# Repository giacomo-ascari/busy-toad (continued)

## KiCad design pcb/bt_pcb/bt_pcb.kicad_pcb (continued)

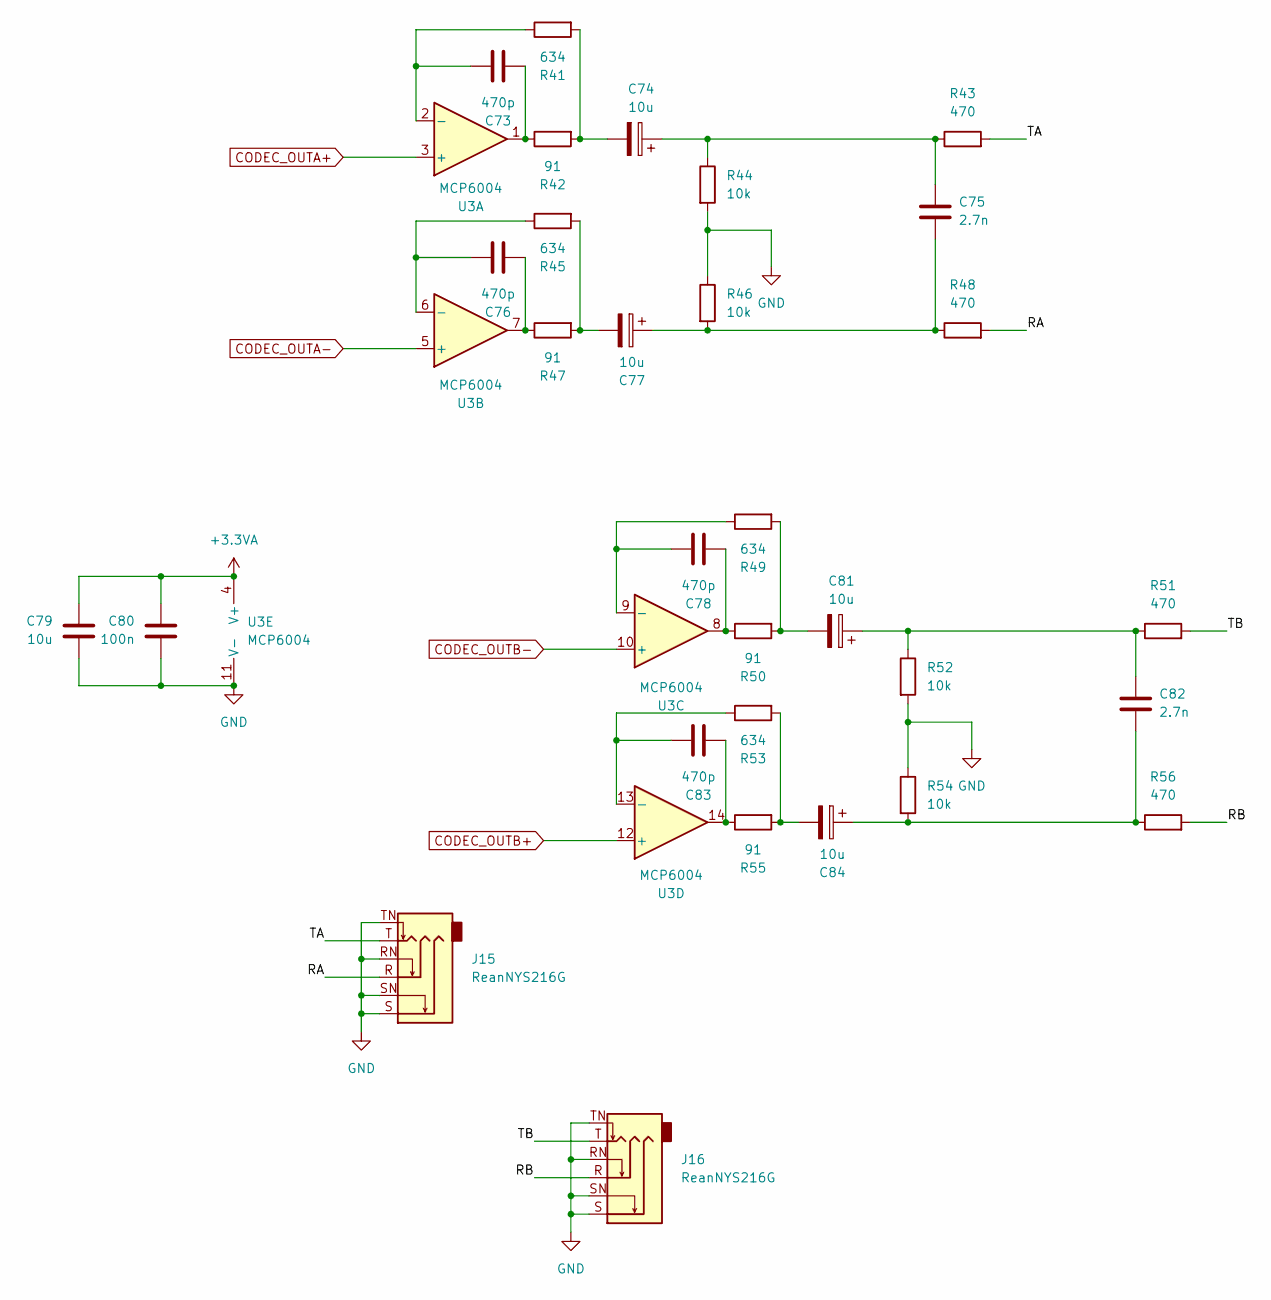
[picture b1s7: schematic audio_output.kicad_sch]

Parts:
C73, C76, C78, C83: 470p; C_0603_1608Metric_Pad1.08x0.95mm_HandSolder
C74, C77, C79, C81, C84: 10u; C_0805_2012Metric_Pad1.18x1.45mm_HandSolder
C75, C82: 2.7n; C_0603_1608Metric_Pad1.08x0.95mm_HandSolder
C80: 100n; C_0603_1608Metric_Pad1.08x0.95mm_HandSolder
J15, J16: ReanNYS216G; NYS-216G
R41, R45, R49, R53: 634; R_0603_1608Metric_Pad0.98x0.95mm_HandSolder
R42, R47, R50, R55: 91; R_0603_1608Metric_Pad0.98x0.95mm_HandSolder
R43, R48, R51, R56: 470; R_0603_1608Metric_Pad0.98x0.95mm_HandSolder
R44, R46, R52, R54: 10k; R_0603_1608Metric_Pad0.98x0.95mm_HandSolder
U3: MCP6004; TSSOP-14_4.4x5mm_P0.65mm

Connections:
+3.3VA: C79.1, C80.1, U3.4 (V+); also elsewhere on the board
/Codec and audio IO/Audio ouput/RA: J15.R, R48.2
/Codec and audio IO/Audio ouput/RB: J16.R, R56.2
/Codec and audio IO/Audio ouput/TA: J15.T, R43.2
/Codec and audio IO/Audio ouput/TB: J16.T, R51.2
CODEC_OUTA+: U3.3 (+); also elsewhere on the board
CODEC_OUTA-: U3.5 (+); also elsewhere on the board
CODEC_OUTB+: U3.12 (+); also elsewhere on the board
CODEC_OUTB-: U3.10 (+); also elsewhere on the board
GND: C79.2, C80.2, J15.RN, J15.S, J15.SN, J15.TN, J16.RN, J16.S, J16.SN, J16.TN, R44.2, R46.1, R52.2, R54.1, U3.11 (V-); also elsewhere on the board
unnamed: C73.1, R42.1, U3.1
unnamed: C74.1, C75.1, R43.1, R44.1
unnamed: C74.2, R41.2, R42.2
unnamed: C75.2, C77.1, R46.2, R48.1
unnamed: C76.1, R47.1, U3.7
unnamed: C77.2, R45.2, R47.2
unnamed: C78.1, R50.1, U3.8
unnamed: C81.1, C82.1, R51.1, R52.1
unnamed: C81.2, R49.2, R50.2
unnamed: C82.2, C84.1, R54.2, R56.1
unnamed: C83.1, R55.1, U3.14
unnamed: C84.2, R53.2, R55.2
unnamed: C73.2, R41.1, U3.2 (-)
unnamed: C76.2, R45.1, U3.6 (-)
unnamed: C78.2, R49.1, U3.9 (-)
unnamed: C83.2, R53.1, U3.13 (-)

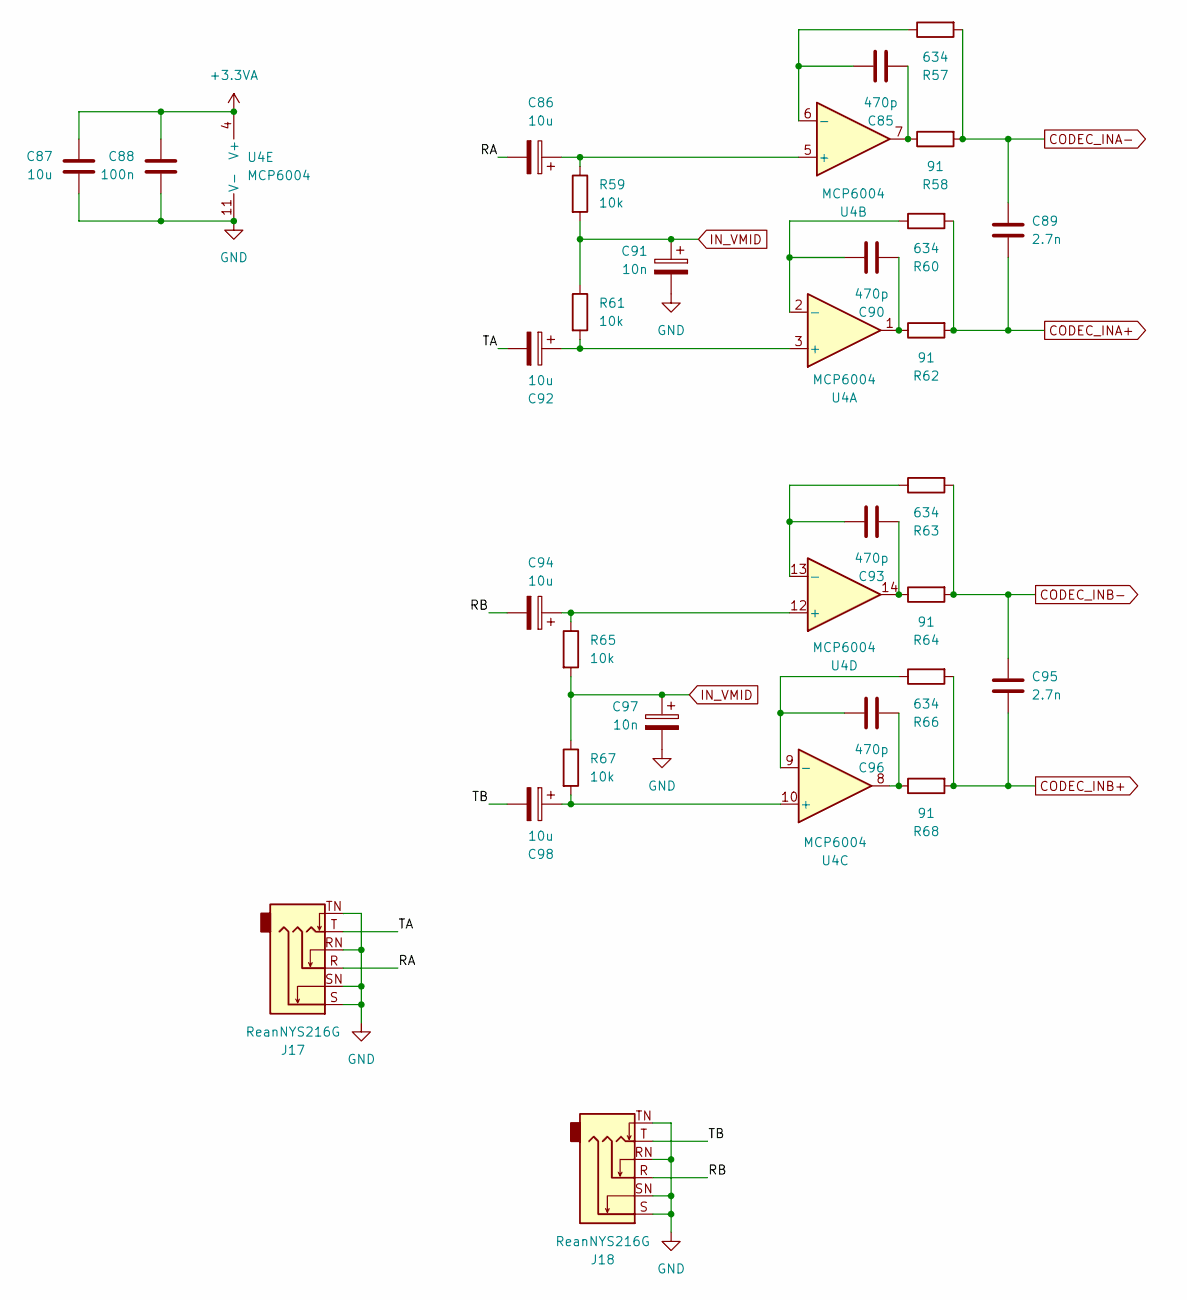
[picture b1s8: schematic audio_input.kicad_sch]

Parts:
C85, C90, C93, C96: 470p; C_0603_1608Metric_Pad1.08x0.95mm_HandSolder
C86, C87, C92, C94, C98: 10u; C_0805_2012Metric_Pad1.18x1.45mm_HandSolder
C88: 100n; C_0603_1608Metric_Pad1.08x0.95mm_HandSolder
C89, C95: 2.7n; C_0603_1608Metric_Pad1.08x0.95mm_HandSolder
C91, C97: 10n; C_0603_1608Metric_Pad1.08x0.95mm_HandSolder
J17, J18: ReanNYS216G; NYS-216G
R57, R60, R63, R66: 634; R_0603_1608Metric_Pad0.98x0.95mm_HandSolder
R58, R62, R64, R68: 91; R_0603_1608Metric_Pad0.98x0.95mm_HandSolder
R59, R61, R65, R67: 10k; R_0603_1608Metric_Pad0.98x0.95mm_HandSolder
U4: MCP6004; TSSOP-14_4.4x5mm_P0.65mm

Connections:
+3.3VA: C87.1, C88.1, U4.4 (V+); also elsewhere on the board
/Codec and audio IO/Audio input/RA: C86.2, J17.R
/Codec and audio IO/Audio input/RB: C94.2, J18.R
/Codec and audio IO/Audio input/TA: C92.2, J17.T
/Codec and audio IO/Audio input/TB: C98.2, J18.T
CODEC_INA+: C89.2, R60.2, R62.2; also elsewhere on the board
CODEC_INA-: C89.1, R57.2, R58.2; also elsewhere on the board
CODEC_INB+: C95.2, R66.2, R68.2; also elsewhere on the board
CODEC_INB-: C95.1, R63.2, R64.2; also elsewhere on the board
GND: C87.2, C88.2, C91.2, C97.2, J17.RN, J17.S, J17.SN, J17.TN, J18.RN, J18.S, J18.SN, J18.TN, U4.11 (V-); also elsewhere on the board
IN_VMID: C91.1, C97.1, R59.2, R61.1, R65.2, R67.1; also elsewhere on the board
unnamed: C85.1, R58.1, U4.7
unnamed: C90.1, R62.1, U4.1
unnamed: C93.1, R64.1, U4.14
unnamed: C96.1, R68.1, U4.8
unnamed: C92.1, R61.2, U4.3 (+)
unnamed: C90.2, R60.1, U4.2 (-)
unnamed: C86.1, R59.1, U4.5 (+)
unnamed: C85.2, R57.1, U4.6 (-)
unnamed: C98.1, R67.2, U4.10 (+)
unnamed: C96.2, R66.1, U4.9 (-)
unnamed: C94.1, R65.1, U4.12 (+)
unnamed: C93.2, R63.1, U4.13 (-)

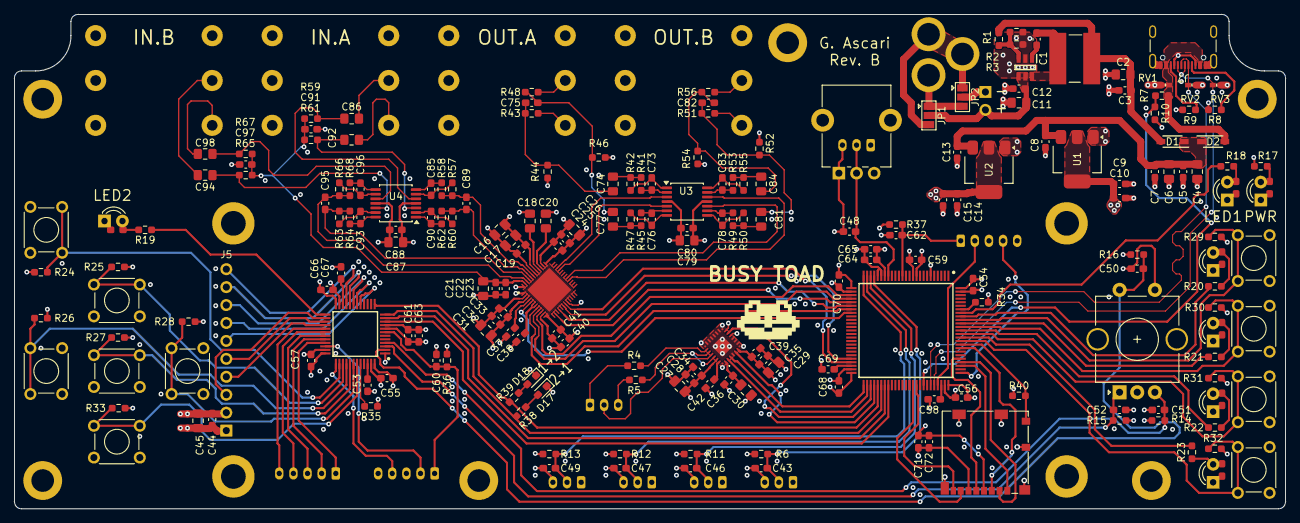
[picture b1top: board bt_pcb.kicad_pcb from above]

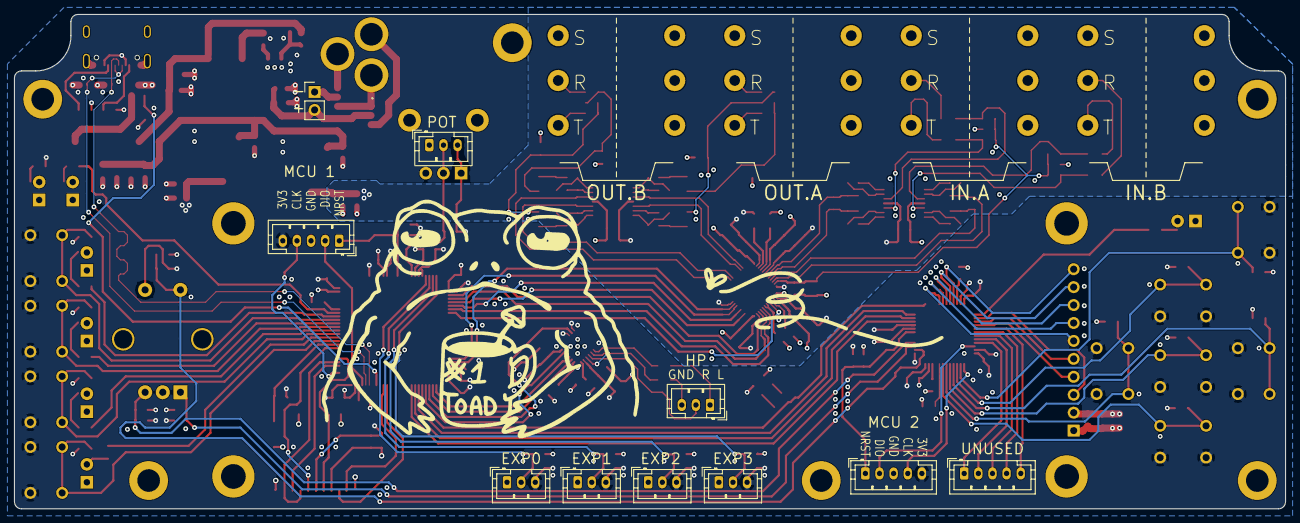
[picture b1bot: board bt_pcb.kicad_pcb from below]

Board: 4 copper layers, 180.0 x 70.0 mm, 235 parts (15 on the bottom side), 154 nets.

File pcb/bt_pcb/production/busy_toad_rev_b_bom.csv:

Designator,Footprint,Quantity,Value,LCSC Part #
"C1, C10, C12, C15, C19, C22, C23, C24, C3, C33, C34, C36, C39, C41, C43, C44, C46, C47, C48, C49, C5, C50, C51, C52, C54, C55, C56, C57, C59, C60, C61, C62, C64, C66, C68, C7, C70, C80, C88",0603,39,100n,
"C11, C17, C2, C26, C27, C29, C30, C31, C4, C45, C6, C74, C77, C79, C81, C84, C86, C87, C92, C94, C98",0805,21,10u,
"C13, C25, C28, C32, C35, C37, C38, C40, C42, C63, C65, C8",0603,12,1u,
"C14, C53, C58, C67, C69, C71, C72, C9",0603,8,2.2u,
"C16, C18, C20, C21",0805,4,22u,
"C73, C76, C78, C83, C85, C90, C93, C96",0603,8,470p,
"C75, C82, C89, C95",0603,4,2.7n,
"C91, C97",0603,2,10n,
"D1, D2",SOD3716X125N,2,B5819W,
"D10, D12, D14, D16, D4, D6, D8",LED_D3.0mm,7,LED,
"D11, D13, D15, D17, D18, D3, D5, D7, D9",0603,9,LED,
IC1,SOT95P280X145-6N,1,LV3842XDBVR,
IC2,QFN40P600X600X80-49N-D,1,CS4282P,
IC3,TAD5242IRGER,1,TAD5242IRGER,
IC4,QFP50P1600X1600X160-100N,1,STM32H750VBT6,
IC5,QFP50P900X900X160-48N,1,STM32H523CET6,
J14,microSD_HC_Molex_104031-0811,1,Micro_SD_Card_Det2,
"J15, J16, J17, J18",NYS-216G,4,ReanNYS216G,
J2,694106301002_1,1,Barrel_Jack_Switch,
J7,USB_C_Receptacle_GCT_USB4105-xx-A_16P_TopMnt_Horizontal,1,USB_C_Receptacle_USB2.0_16P,
L1,SRR6040A180M,1,18uH 1.5A,
R1,0603,1,100k,
"R10, R11, R12, R13, R14, R15, R16, R24, R25, R26, R27, R28, R29, R30, R31, R32, R33, R34, R35, R36, R37, R40, R44, R46, R52, R54, R59, R6, R61, R65, R67",0603,31,10k,
"R17, R18, R19, R20, R21, R22, R23",0603,7,680/510,
"R2, R3",0603,2,47k,
"R38, R39",0603,2,680,
"R4, R5",0603,2,22,
"R41, R45, R49, R53, R57, R60, R63, R66",0603,8,634,
"R42, R47, R50, R55, R58, R62, R64, R68",0603,8,91,
"R43, R48, R51, R56",0603,4,470,
R7,0603,1,4k7,
"R8, R9",0603,2,5k1,
"RV1, RV2, RV3",VARC1005X41N,3,CG0402MLU-12G,
RV4,Potentiometer_Alpha_RD901F-40-00D_Single_Vertical_CircularHoles,1,R_Potentiometer,
SW1,RotaryEncoder_Alps_EC11E-Switch_Vertical_H20mm_CircularMountingHoles,1,RotaryEncoder_Switch,
"SW10, SW11, SW2, SW3, SW4, SW5, SW6, SW7, SW8, SW9",SW_TH_Tactile_Omron_B3F-102x,10,SW_Push,
"U1, U2",SOT-223-3_TabPin2,2,TLV76133DCY,
"U3, U4",TSSOP-14_4.4x5mm_P0.65mm,2,MCP6004,

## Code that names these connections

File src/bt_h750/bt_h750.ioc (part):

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Mcu.Name=STM32H750VBTx
Mcu.Package=LQFP100
Mcu.UserName=STM32H750VBTx
PA0.GPIOParameters=GPIO_Label
PA0.GPIO_Label=EXP_0
PA0.Mode=IN16-Single-Ended
PA0.Signal=ADC1_INP16
PA1.GPIOParameters=GPIO_Label
PA1.GPIO_Label=EXP_1
PA1.Mode=IN17-Single-Ended
PA1.Signal=ADC1_INP17
PA10.GPIOParameters=GPIO_Label,GPIO_Pd
PA10.GPIO_Label=X
PA10.GPIO_Pd=GPIO_PULLDOWN
PA10.Signal=GPIO_Analog
PA11.Mode=Device_Only
PA11.Signal=USB_OTG_FS_DM
PA12.Mode=Device_Only
PA12.Signal=USB_OTG_FS_DP
PA13\ (JTMS/SWDIO).Mode=Serial_Wire
PA13\ (JTMS/SWDIO).Signal=DEBUG_JTMS-SWDIO
PA14\ (JTCK/SWCLK).Mode=Serial_Wire
PA14\ (JTCK/SWCLK).Signal=DEBUG_JTCK-SWCLK
PA15\ (JTDI).GPIOParameters=GPIO_Label,GPIO_Pd
PA15\ (JTDI).GPIO_Label=X
PA15\ (JTDI).GPIO_Pd=GPIO_PULLDOWN
PA15\ (JTDI).Signal=GPIO_Analog
PA2.GPIOParameters=GPIO_Label
PA2.GPIO_Label=EXP_2
PA2.Signal=ADCx_INP14
PA3.GPIOParameters=GPIO_Label
PA3.GPIO_Label=EXP_3
PA3.Signal=ADCx_INP15
PA4.GPIOParameters=GPIO_Label
PA4.GPIO_Label=CODEC_I2S_WS
PA4.Mode=Full_Duplex_Master
PA4.Signal=I2S1_WS
PA5.GPIOParameters=GPIO_Label
PA5.GPIO_Label=CODEC_I2S_CK
PA5.Mode=Full_Duplex_Master
PA5.Signal=I2S1_CK
PA6.GPIOParameters=GPIO_Label
PA6.GPIO_Label=CODEC_I2S_SDI
PA6.Mode=Full_Duplex_Master
PA6.Signal=I2S1_SDI
PA7.GPIOParameters=GPIO_Label
PA7.GPIO_Label=CODEC_I2S_SDO
PA7.Mode=Full_Duplex_Master
PA7.Signal=I2S1_SDO
PA8.GPIOParameters=GPIO_Label,GPIO_Pd
PA8.GPIO_Label=X
PA8.GPIO_Pd=GPIO_PULLDOWN
PA8.Signal=GPIO_Analog
PA9.Mode=Activate_VBUS
PA9.Signal=USB_OTG_FS_VBUS
PB0.GPIOParameters=GPIO_Label,GPIO_Pd
PB0.GPIO_Label=X
PB0.GPIO_Pd=GPIO_PULLDOWN
PB0.Signal=GPIO_Analog
PB1.GPIOParameters=GPIO_Label,GPIO_Pd
PB1.GPIO_Label=X
PB1.GPIO_Pd=GPIO_PULLDOWN
PB1.Signal=GPIO_Analog
PB10.GPIOParameters=GPIO_Speed,GPIO_Label,GPIO_Pu
PB10.GPIO_Label=CODEC_I2C_SCL
PB10.GPIO_Pu=GPIO_NOPULL
PB10.GPIO_Speed=GPIO_SPEED_FREQ_LOW
PB10.Mode=I2C
PB10.Signal=I2C2_SCL
PB11.GPIOParameters=GPIO_Speed,GPIO_Label,GPIO_Pu
PB11.GPIO_Label=CODEC_I2C_SDA
PB11.GPIO_Pu=GPIO_NOPULL
PB11.GPIO_Speed=GPIO_SPEED_FREQ_LOW
PB11.Mode=I2C
PB11.Signal=I2C2_SDA
PB12.GPIOParameters=GPIO_Speed,GPIO_Label
PB12.GPIO_Label=HPDAC_I2S_WS
PB12.GPIO_Speed=GPIO_SPEED_FREQ_LOW
PB12.Mode=Full_Duplex_Master
PB12.Signal=I2S2_WS
PB13.GPIOParameters=GPIO_Speed,GPIO_Label
PB13.GPIO_Label=HPDAC_I2S_BCK
PB13.GPIO_Speed=GPIO_SPEED_FREQ_LOW
PB13.Mode=Full_Duplex_Master
PB13.Signal=I2S2_CK
PB14.GPIOParameters=GPIO_Speed,GPIO_Label
PB14.GPIO_Label=HPDAC_I2S_SDI
PB14.GPIO_Speed=GPIO_SPEED_FREQ_LOW
PB14.Mode=Full_Duplex_Master
PB14.Signal=I2S2_SDI
PB15.GPIOParameters=GPIO_Speed,GPIO_Label
PB15.GPIO_Label=HPDAC_I2S_SDO
PB15.GPIO_Speed=GPIO_SPEED_FREQ_LOW
PB15.Mode=Full_Duplex_Master
PB15.Signal=I2S2_SDO
PB2.GPIOParameters=GPIO_Label,GPIO_Pd
PB2.GPIO_Label=X
PB2.GPIO_Pd=GPIO_PULLDOWN
PB2.Signal=GPIO_Analog
PB3\ (JTDO/TRACESWO).GPIOParameters=GPIO_Label
PB3\ (JTDO/TRACESWO).GPIO_Label=BTN_B
PB3\ (JTDO/TRACESWO).Signal=GPIO_Input
PB4\ (NJTRST).GPIOParameters=GPIO_Label
PB4\ (NJTRST).GPIO_Label=LED_B
PB4\ (NJTRST).Signal=GPIO_Output
PB5.GPIOParameters=GPIO_Label
PB5.GPIO_Label=BTN_A
PB5.Signal=GPIO_Input
PB6.GPIOParameters=GPIO_Label
PB6.GPIO_Label=LED_A
PB6.Signal=GPIO_Output
PB7.GPIOParameters=GPIO_Label
PB7.GPIO_Label=LED_RD
PB7.Signal=GPIO_Output
PB8.GPIOParameters=GPIO_Label,GPIO_Pd
PB8.GPIO_Label=X
PB8.GPIO_Pd=GPIO_PULLDOWN
PB8.Signal=GPIO_Analog
PB9.GPIOParameters=GPIO_Label,GPIO_Pd
PB9.GPIO_Label=X
PB9.GPIO_Pd=GPIO_PULLDOWN
PB9.Signal=GPIO_Analog
PC0.GPIOParameters=GPIO_Label,GPIO_Pd
PC0.GPIO_Label=X
PC0.GPIO_Pd=GPIO_PULLDOWN
PC0.Signal=GPIO_Analog
PC1.GPIOParameters=GPIO_Label,GPIO_Pd
PC1.GPIO_Label=X
PC1.GPIO_Pd=GPIO_PULLDOWN
PC1.Signal=GPIO_Analog
PC10.GPIOParameters=GPIO_PuPd,GPIO_Speed_High_Default,GPIO_Label
PC10.GPIO_Label=SD_D2
PC10.GPIO_PuPd=GPIO_PULLUP
PC10.GPIO_Speed_High_Default=GPIO_SPEED_FREQ_LOW
PC10.Mode=SD_4_bits_Wide_bus
PC10.Signal=SDMMC1_D2
PC11.GPIOParameters=GPIO_PuPd,GPIO_Speed_High_Default,GPIO_Label
PC11.GPIO_Label=SD_D3
PC11.GPIO_PuPd=GPIO_PULLUP
PC11.GPIO_Speed_High_Default=GPIO_SPEED_FREQ_LOW
PC11.Mode=SD_4_bits_Wide_bus
PC11.Signal=SDMMC1_D3
PC12.GPIOParameters=GPIO_Speed_High_Default,GPIO_Label
PC12.GPIO_Label=SD_CK
PC12.GPIO_Speed_High_Default=GPIO_SPEED_FREQ_LOW
PC12.Mode=SD_4_bits_Wide_bus
PC12.Signal=SDMMC1_CK
PC13.GPIOParameters=GPIO_Label,GPIO_Pd
PC13.GPIO_Label=X
PC13.GPIO_Pd=GPIO_PULLDOWN
PC13.Signal=GPIO_Analog
PC14-OSC32_IN\ (OSC32_IN).GPIOParameters=GPIO_Label,GPIO_Pd
PC14-OSC32_IN\ (OSC32_IN).GPIO_Label=X
PC14-OSC32_IN\ (OSC32_IN).GPIO_Pd=GPIO_PULLDOWN
PC14-OSC32_IN\ (OSC32_IN).Signal=GPIO_Analog
PC15-OSC32_OUT\ (OSC32_OUT).GPIOParameters=GPIO_Label,GPIO_Pd
PC15-OSC32_OUT\ (OSC32_OUT).GPIO_Label=X
PC15-OSC32_OUT\ (OSC32_OUT).GPIO_Pd=GPIO_PULLDOWN
PC15-OSC32_OUT\ (OSC32_OUT).Signal=GPIO_Analog
PC2_C.GPIOParameters=GPIO_Label,GPIO_Pd
PC2_C.GPIO_Label=X
PC2_C.GPIO_Pd=GPIO_PULLDOWN
PC2_C.Signal=GPIO_Analog
PC3_C.GPIOParameters=GPIO_Label
PC3_C.GPIO_Label=POT_0
PC3_C.Mode=IN1-Single-Ended
PC3_C.Signal=ADC3_INP1
PC4.GPIOParameters=GPIO_Label
PC4.GPIO_Label=CODEC_I2S_MCK
PC4.Mode=Master_Clock_Activated
PC4.Signal=I2S1_MCK
PC5.GPIOParameters=GPIO_Label
PC5.GPIO_Label=CODEC_RESET
PC5.Signal=GPIO_Output
PC6.GPIOParameters=GPIO_Label,GPIO_Pd
PC6.GPIO_Label=X
PC6.GPIO_Pd=GPIO_PULLDOWN
PC6.Signal=GPIO_Analog
PC7.GPIOParameters=GPIO_Label,GPIO_Pd
PC7.GPIO_Label=X
PC7.GPIO_Pd=GPIO_PULLDOWN
PC7.Signal=GPIO_Analog
PC8.GPIOParameters=GPIO_PuPd,GPIO_Speed_High_Default,GPIO_Label
PC8.GPIO_Label=SD_D0
PC8.GPIO_PuPd=GPIO_PULLUP
PC8.GPIO_Speed_High_Default=GPIO_SPEED_FREQ_LOW
PC8.Mode=SD_4_bits_Wide_bus
PC8.Signal=SDMMC1_D0
PC9.GPIOParameters=GPIO_PuPd,GPIO_Speed_High_Default,GPIO_Label
PC9.GPIO_Label=SD_D1
PC9.GPIO_PuPd=GPIO_PULLUP
PC9.GPIO_Speed_High_Default=GPIO_SPEED_FREQ_LOW
PC9.Mode=SD_4_bits_Wide_bus
PC9.Signal=SDMMC1_D1
PD0.GPIOParameters=GPIO_Label,GPIO_Pd
PD0.GPIO_Label=X
PD0.GPIO_Pd=GPIO_PULLDOWN
PD0.Signal=GPIO_Analog
PD1.GPIOParameters=GPIO_Label,GPIO_Pd
PD1.GPIO_Label=X
PD1.GPIO_Pd=GPIO_PULLDOWN
PD1.Signal=GPIO_Analog
PD10.GPIOParameters=GPIO_Label
PD10.GPIO_Label=AUX_OUTPUT
PD10.Signal=GPIO_Output
PD11.GPIOParameters=GPIO_Label
PD11.GPIO_Label=AUX_INPUT
PD11.Signal=GPIO_Input
PD12.GPIOParameters=GPIO_Label,GPIO_Pd
PD12.GPIO_Label=X
PD12.GPIO_Pd=GPIO_PULLDOWN
PD12.Signal=GPIO_Analog
PD13.GPIOParameters=GPIO_Label,GPIO_Pd
PD13.GPIO_Label=X
PD13.GPIO_Pd=GPIO_PULLDOWN
PD13.Signal=GPIO_Analog
PD14.GPIOParameters=GPIO_Label,GPIO_Pd
PD14.GPIO_Label=X
PD14.GPIO_Pd=GPIO_PULLDOWN
PD14.Signal=GPIO_Analog
PD15.GPIOParameters=GPIO_Label,GPIO_Pd
PD15.GPIO_Label=X
PD15.GPIO_Pd=GPIO_PULLDOWN
PD15.Signal=GPIO_Analog
PD2.GPIOParameters=GPIO_PuPd,GPIO_Speed_High_Default,GPIO_Label
PD2.GPIO_Label=SD_CMD
PD2.GPIO_PuPd=GPIO_PULLUP
PD2.GPIO_Speed_High_Default=GPIO_SPEED_FREQ_LOW
PD2.Mode=SD_4_bits_Wide_bus
PD2.Signal=SDMMC1_CMD
PD3.GPIOParameters=GPIO_Label
PD3.GPIO_Label=SD_DETECT
PD3.Signal=GPIO_Input
PD4.GPIOParameters=GPIO_Label
PD4.GPIO_Label=BTN_D
PD4.Signal=GPIO_Input
PD5.GPIOParameters=GPIO_Label
PD5.GPIO_Label=LED_D
PD5.Signal=GPIO_Output
PD6.GPIOParameters=GPIO_Label
PD6.GPIO_Label=BTN_C
PD6.Signal=GPIO_Input
PD7.GPIOParameters=GPIO_Label
PD7.GPIO_Label=LED_C
PD7.Signal=GPIO_Output
PD8.GPIOParameters=GPIO_Label
PD8.GPIO_Label=USART_TX
PD8.Mode=Asynchronous
PD8.Signal=USART3_TX
PD9.GPIOParameters=GPIO_Label
PD9.GPIO_Label=USART_RX
PD9.Mode=Asynchronous
PD9.Signal=USART3_RX
PE0.GPIOParameters=GPIO_Label,GPIO_Pd
PE0.GPIO_Label=X
PE0.GPIO_Pd=GPIO_PULLDOWN
PE0.Signal=GPIO_Analog
PE1.GPIOParameters=GPIO_Label,GPIO_Pd
PE1.GPIO_Label=X
PE1.GPIO_Pd=GPIO_PULLDOWN
PE1.Signal=GPIO_Analog
PE10.GPIOParameters=GPIO_Label,GPIO_Pd
PE10.GPIO_Label=X
PE10.GPIO_Pd=GPIO_PULLDOWN
PE10.Signal=GPIO_Analog
PE11.GPIOParameters=GPIO_Label,GPIO_Pd
PE11.GPIO_Label=X
PE11.GPIO_Pd=GPIO_PULLDOWN
PE11.Signal=GPIO_Analog
PE12.GPIOParameters=GPIO_Label,GPIO_Pd
PE12.GPIO_Label=X
PE12.GPIO_Pd=GPIO_PULLDOWN
PE12.Signal=GPIO_Analog
PE13.GPIOParameters=GPIO_Label,GPIO_Pd
PE13.GPIO_Label=X
PE13.GPIO_Pd=GPIO_PULLDOWN
PE13.Signal=GPIO_Analog
PE14.GPIOParameters=GPIO_Label,GPIO_Pd
PE14.GPIO_Label=X
PE14.GPIO_Pd=GPIO_PULLDOWN
PE14.Signal=GPIO_Analog
PE15.GPIOParameters=GPIO_Label,GPIO_Pd
PE15.GPIO_Label=X
PE15.GPIO_Pd=GPIO_PULLDOWN
PE15.Signal=GPIO_Analog
PE2.GPIOParameters=GPIO_Label,GPIO_Pd
PE2.GPIO_Label=X
PE2.GPIO_Pd=GPIO_PULLDOWN
PE2.Signal=GPIO_Analog
PE3.GPIOParameters=GPIO_Label,GPIO_Pd
PE3.GPIO_Label=X
PE3.GPIO_Pd=GPIO_PULLDOWN
PE3.Signal=GPIO_Analog
PE4.GPIOParameters=GPIO_Label,GPIO_Pd
PE4.GPIO_Label=X
PE4.GPIO_Pd=GPIO_PULLDOWN
PE4.Signal=GPIO_Analog
PE5.GPIOParameters=GPIO_Label,GPIO_Pd
PE5.GPIO_Label=X
PE5.GPIO_Pd=GPIO_PULLDOWN
PE5.Signal=GPIO_Analog
PE6.GPIOParameters=GPIO_Label,GPIO_Pd
PE6.GPIO_Label=X
PE6.GPIO_Pd=GPIO_PULLDOWN
PE6.Signal=GPIO_Analog
PE7.GPIOParameters=GPIO_Label,GPIO_Pd
PE7.GPIO_Label=X
PE7.GPIO_Pd=GPIO_PULLDOWN
PE7.Signal=GPIO_Analog
PE8.GPIOParameters=GPIO_Label,GPIO_Pd
PE8.GPIO_Label=X
PE8.GPIO_Pd=GPIO_PULLDOWN
PE8.Signal=GPIO_Analog
PE9.GPIOParameters=GPIO_Label,GPIO_Pd

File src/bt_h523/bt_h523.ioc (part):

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Mcu.Name=STM32H523CETx
Mcu.Package=LQFP48
Mcu.UserName=STM32H523CETx
PA0.GPIOParameters=GPIO_Label
PA0.GPIO_Label=AUX_OUTPUT
PA0.Signal=GPIO_Output
PA1.GPIOParameters=GPIO_Label
PA1.GPIO_Label=AUX_INPUT
PA1.Signal=GPIO_Input
PA10.GPIOParameters=GPIO_Label,GPIO_Pd,GPIO_Mode
PA10.GPIO_Label=X
PA10.GPIO_Mode=GPIO_MODE_ANALOG
PA10.GPIO_Pd=GPIO_PULLDOWN
PA10.Signal=GPIO_Analog
PA11.GPIOParameters=GPIO_Label,GPIO_Pd,GPIO_Mode
PA11.GPIO_Label=X
PA11.GPIO_Mode=GPIO_MODE_ANALOG
PA11.GPIO_Pd=GPIO_PULLDOWN
PA11.Signal=GPIO_Analog
PA12.GPIOParameters=GPIO_Label,GPIO_Pd,GPIO_Mode
PA12.GPIO_Label=X
PA12.GPIO_Mode=GPIO_MODE_ANALOG
PA12.GPIO_Pd=GPIO_PULLDOWN
PA12.Signal=GPIO_Analog
PA13(JTMS/SWDIO).Mode=Serial_Wire
PA13(JTMS/SWDIO).Signal=DEBUG_JTMS-SWDIO
PA14(JTCK/SWCLK).Mode=Serial_Wire
PA14(JTCK/SWCLK).Signal=DEBUG_JTCK-SWCLK
PA15(JTDI).GPIOParameters=GPIO_Label
PA15(JTDI).GPIO_Label=BTN_F
PA15(JTDI).Signal=GPIO_Input
PA2.GPIOParameters=GPIO_Label
PA2.GPIO_Label=USART_TX
PA2.Mode=Asynchronous
PA2.Signal=USART2_TX
PA3.GPIOParameters=GPIO_Label
PA3.GPIO_Label=USART_RX
PA3.Mode=Asynchronous
PA3.Signal=USART2_RX
PA4.GPIOParameters=GPIO_Label,GPIO_Pd,GPIO_Mode
PA4.GPIO_Label=X
PA4.GPIO_Mode=GPIO_MODE_ANALOG
PA4.GPIO_Pd=GPIO_PULLDOWN
PA4.Signal=GPIO_Analog
PA5.GPIOParameters=GPIO_Label,GPIO_Pd,GPIO_Mode
PA5.GPIO_Label=X
PA5.GPIO_Mode=GPIO_MODE_ANALOG
PA5.GPIO_Pd=GPIO_PULLDOWN
PA5.Signal=GPIO_Analog
PA6.GPIOParameters=GPIO_Label,GPIO_Pd,GPIO_Mode
PA6.GPIO_Label=X
PA6.GPIO_Mode=GPIO_MODE_ANALOG
PA6.GPIO_Pd=GPIO_PULLDOWN
PA6.Signal=GPIO_Analog
PA7.GPIOParameters=GPIO_Label
PA7.GPIO_Label=DP_GPIO_0
PA7.Signal=GPIO_Output
PA8.GPIOParameters=GPIO_Label,GPIO_Pd,GPIO_Mode
PA8.GPIO_Label=X
PA8.GPIO_Mode=GPIO_MODE_ANALOG
PA8.GPIO_Pd=GPIO_PULLDOWN
PA8.Signal=GPIO_Analog
PA9.GPIOParameters=GPIO_Label,GPIO_Pd,GPIO_Mode
PA9.GPIO_Label=X
PA9.GPIO_Mode=GPIO_MODE_ANALOG
PA9.GPIO_Pd=GPIO_PULLDOWN
PA9.Signal=GPIO_Analog
PB0.GPIOParameters=GPIO_Label
PB0.GPIO_Label=DP_GPIO_1
PB0.Signal=GPIO_Output
PB1.GPIOParameters=GPIO_Label
PB1.GPIO_Label=DP_GPIO_2
PB1.Signal=GPIO_Output
PB10.GPIOParameters=GPIO_Label
PB10.GPIO_Label=DP_GPIO_4
PB10.Signal=GPIO_Output
PB12.GPIOParameters=GPIO_Label
PB12.GPIO_Label=LED_RD
PB12.Signal=GPIO_Output
PB13.GPIOParameters=GPIO_Label
PB13.GPIO_Label=DP_SPI_SCK
PB13.Mode=Full_Duplex_Master
PB13.Signal=SPI2_SCK
PB14.GPIOParameters=GPIO_Label
PB14.GPIO_Label=DP_SPI_MISO
PB14.Mode=Full_Duplex_Master
PB14.Signal=SPI2_MISO
PB15.GPIOParameters=GPIO_Label
PB15.GPIO_Label=DP_SPI_MOSI
PB15.Mode=Full_Duplex_Master
PB15.Signal=SPI2_MOSI
PB2.GPIOParameters=GPIO_Label
PB2.GPIO_Label=DP_GPIO_3
PB2.Signal=GPIO_Output
PB3(JTDO/TRACESWO).GPIOParameters=GPIO_Label
PB3(JTDO/TRACESWO).GPIO_Label=BTN_E
PB3(JTDO/TRACESWO).Signal=GPIO_Input
PB4(NJTRST).GPIOParameters=GPIO_Label
PB4(NJTRST).GPIO_Label=BTN_D
PB4(NJTRST).Signal=GPIO_Input
PB5.GPIOParameters=GPIO_Label
PB5.GPIO_Label=BTN_C
PB5.Signal=GPIO_Input
PB6.GPIOParameters=GPIO_Label
PB6.GPIO_Label=BTN_B
PB6.Signal=GPIO_Input
PB7.GPIOParameters=GPIO_Label
PB7.GPIO_Label=BTN_A
PB7.Signal=GPIO_Input
PB8.GPIOParameters=GPIO_Label,GPIO_Pd,GPIO_Mode
PB8.GPIO_Label=X
PB8.GPIO_Mode=GPIO_MODE_ANALOG
PB8.GPIO_Pd=GPIO_PULLDOWN
PB8.Signal=GPIO_Analog
PC13.GPIOParameters=GPIO_Label
PC13.GPIO_Label=ENC_SW
PC13.Signal=GPIO_Input
PC14-OSC32_IN(OSC32_IN).GPIOParameters=GPIO_Label
PC14-OSC32_IN(OSC32_IN).GPIO_Label=ENC_A
PC14-OSC32_IN(OSC32_IN).Signal=GPIO_Input
PC15-OSC32_OUT(OSC32_OUT).GPIOParameters=GPIO_Label
PC15-OSC32_OUT(OSC32_OUT).GPIO_Label=ENC_B
PC15-OSC32_OUT(OSC32_OUT).Signal=GPIO_Input
PH0-OSC_IN(PH0).GPIOParameters=GPIO_Label,GPIO_Pd,GPIO_Mode
PH0-OSC_IN(PH0).GPIO_Label=X
PH0-OSC_IN(PH0).GPIO_Mode=GPIO_MODE_ANALOG
PH0-OSC_IN(PH0).GPIO_Pd=GPIO_PULLDOWN
PH0-OSC_IN(PH0).Signal=GPIO_Analog
PH1-OSC_OUT(PH1).GPIOParameters=GPIO_Label,GPIO_Pd,GPIO_Mode
PH1-OSC_OUT(PH1).GPIO_Label=X
PH1-OSC_OUT(PH1).GPIO_Mode=GPIO_MODE_ANALOG
PH1-OSC_OUT(PH1).GPIO_Pd=GPIO_PULLDOWN
PH1-OSC_OUT(PH1).Signal=GPIO_Analog
RCC.HSE_VALUE=25000000
RCC.SYSCLKFreq_VALUE=64000000
RCC.SYSCLKSource=RCC_SYSCLKSOURCE_PLLCLK
board=custom

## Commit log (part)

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2023-09-08 some datasheets
2024-01-24 some more docs
2024-02-01 progress
2024-02-05 splash screen empty file
2024-02-05 progress on audio pcb
2024-02-08 progress on understanding audio schematics
2024-02-13 couple of things
2024-02-13 progress on audio in
2024-02-14 progress on audio
2024-02-26 some progress
2024-03-06 some notes for input levels
2024-03-11 progressive rock
2024-10-07 reprising work
2024-10-11 Added system.drawio
2024-10-12 Aggiorna system.drawio
2024-10-14 progress on shcematics
2024-10-16 some invenstigation on the codec circuitry
2024-10-16 i forgot this
2024-10-20 aaaaaa
2024-10-27 some more pages for the schematic
2024-11-03 big progress!
2024-11-19 making up my mind on the heaphones
2024-11-21 progress on hp
2024-11-30 a lot of audio finished, now onto ui
2024-12-01 minor
2024-12-05 a lot of work! almost ready for rev
2024-12-06 schematic finished, now under revision
2024-12-18 starting the revision from ed
2025-02-12 smol
2025-02-18 some docs
2025-03-29 started development on power pcb
2025-10-18 ditching power pcb, new codec
2025-10-20 complete makeover of power supply
2025-10-28 big progress, now revising error and warnings
2025-11-02 solving some erc warnings and errors
2025-11-09 schematic in theory finished
2025-11-09 finished for real, now onto review
2025-11-09 pcb started
2025-11-12 pcb with some schematic tuning
2025-11-12 progress on pcb
2025-11-14 leftovers
2025-11-17 pcb now under revision
2025-11-18 continuing review
2025-11-18 removal of old files
2025-12-01 first notes
2025-12-12 first reiteration
2026-01-11 doing pcb from scratch again
2026-01-11 layed components down
2026-01-22 routing stuff
2026-01-30 almost there
2026-02-01 maybe???
2026-02-10 redo of power supply
2026-02-12 made a bom
2026-02-12 updated and pretty bom
2026-02-18 seeing the end of the tunnel
2026-02-19 font draft and picture on pcb
2026-02-21 order of rev a eheh
2026-03-15 maybe start of coding soon
2026-03-29 going back
2026-04-08 schematics svgs
2026-04-08 starting work on rev b
2026-04-25 new parts
2026-04-26 aaaaaaa
2026-05-05 headphone dac parts
2026-05-09 schematic rev b finish?
2026-05-09 maybe?
2026-05-10 progress!
2026-05-11 just need to fix usb
2026-05-11 whoops
2026-05-12 usb fatta!
2026-05-14 rev b likely finished
2026-05-15 sd card is the way probably :(
2026-05-15 sd kind of in
2026-05-17 wired! now just checking
2026-05-18 led1 now not under the display
2026-05-23 fixed usb impedance
2026-05-23 work on fonts
2026-05-25 bom bom bom
2026-06-03 tweaks
2026-06-04 maybe new dac
2026-06-06 reb b finished
2026-06-06 rev b really finished
